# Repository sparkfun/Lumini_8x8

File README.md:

SparkFun LuMini 8x8 Matrix
========================================

[*SparkFun LuMini LED matrix (COM-15047)*](https://www.sparkfun.com/products/15047)

The LuMini 8x8 Matrix is a great way to add a square of light to just about anything, or even make a screen of a custom shape. The LuMini product line uses the same LED used on our Lumenati boards, the APA102, just in a smaller, 2.0x2.0 mm package. This allows for incredibly tight pixel densities, and thus, a screen with less pixelation. 

Repository Contents
-------------------

* **/Firmware** - Example code 
* **/Hardware** - Eagle design files (.brd, .sch)
* **/Production** - Production panel files (.brd)

Documentation
--------------
* **[Hookup Guide](https://learn.sparkfun.com/tutorials/lumini-8x8-matrix-hookup-guide)** - Basic hookup guide for the LuMini 8x8 LED Matrix.

Product Versions
----------------
* [COM-15047](https://www.sparkfun.com/products/15047)- 8x8 matrix of APA102 LED's packed into a single square inch.

License Information
-------------------

This product is _**open source**_! 

Please review the LICENSE.md file for license information. 

If you have any questions or concerns on licensing, please contact techsupport@sparkfun.com.

Distributed as-is; no warranty is given.

- Your friends at SparkFun.

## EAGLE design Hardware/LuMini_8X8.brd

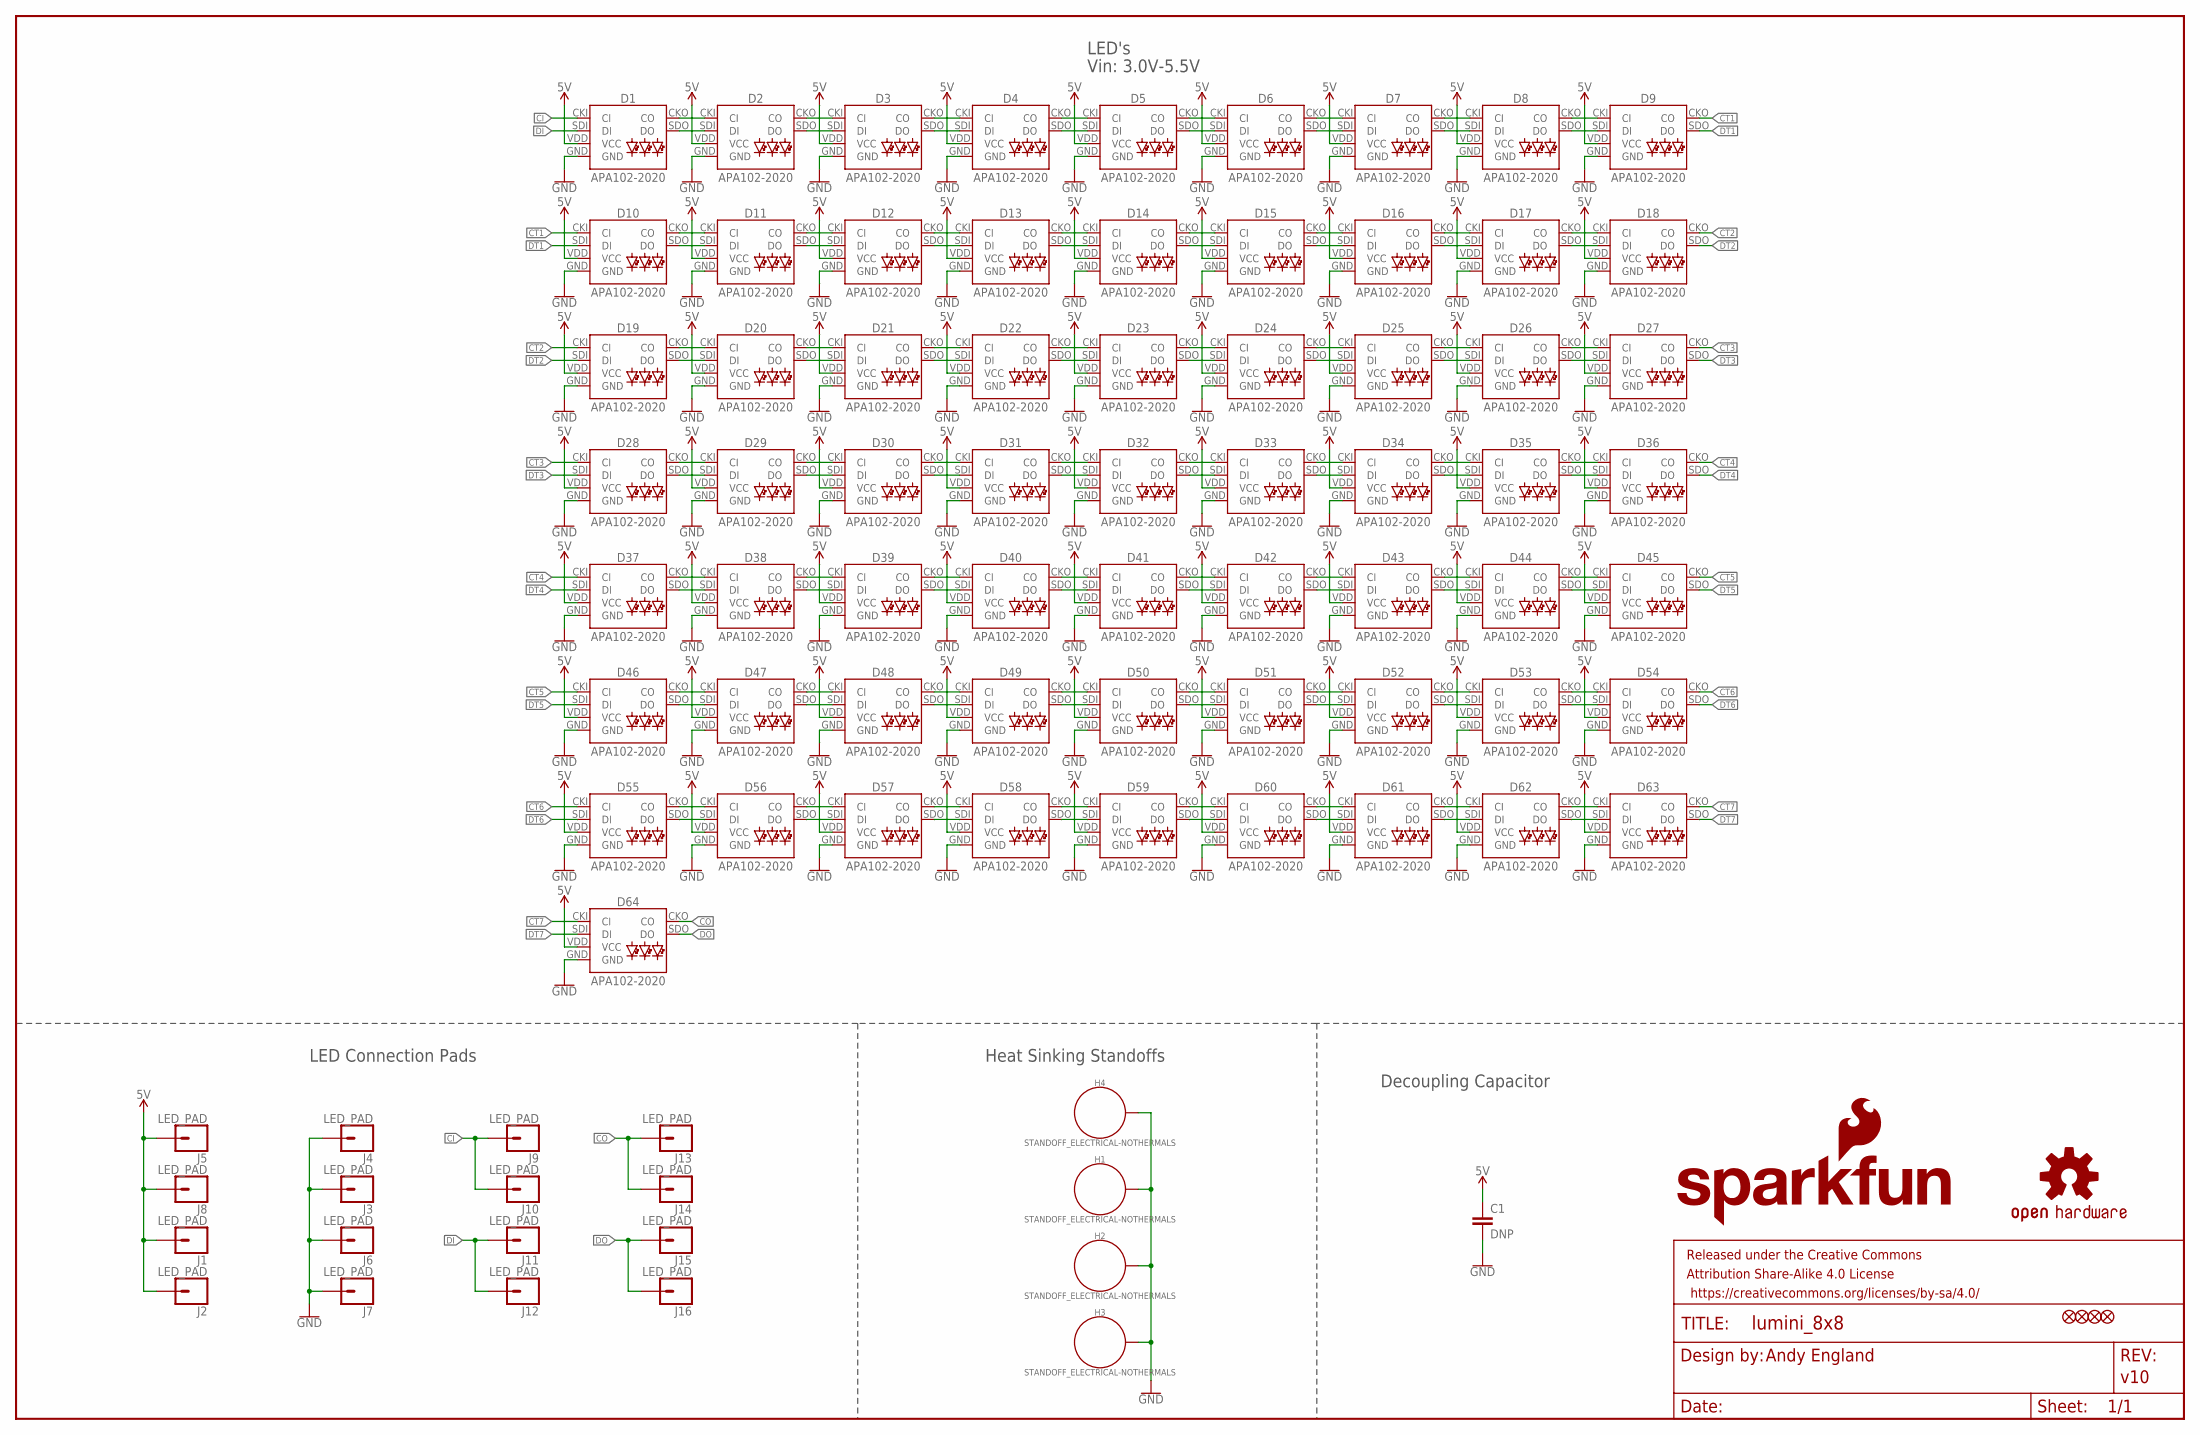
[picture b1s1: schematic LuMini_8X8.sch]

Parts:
C1: DNP; 1206
D1, D2, D3, D4, D5, D6, D7, D8, D9, D10, D11, D12, D13, D14, D15, D16, D17, D18, D19, D20, D21, D22, D23, D24, D25, D26, D27, D28, D29, D30, D31, D32, D33, D34, D35, D36, D37, D38, D39, D40, D41, D42, D43, D44, D45, D46, D47, D48, D49, D50, D51, D52, D53, D54, D55, D56, D57, D58, D59, D60, D61, D62, D63, D64: APA102-2020
FD1, FD2, FD3, FD4: FIDUCIALUFIDUCIAL; FIDUCIAL-MICRO
FRAME1: FRAME-LEDGER; CREATIVE_COMMONS
H1, H2, H3, H4: STANDOFF_ELECTRICAL-NOTHERMALS; STANDOFF-ELECTRICAL-NOTHERMALS
J1, J2, J3, J4, J5, J6, J7, J8, J9, J10, J11, J12, J13, J14, J15, J16: LED_PAD; CIRCULARPAD
LOGO1: SFE_LOGO_NAME_FLAME.1_INCH; SFE_LOGO_NAME_FLAME_.1
LOGO2: OSHW-LOGOS; OSHW-LOGO-S

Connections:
5V: C1.1, D1.VDD (VCC), D2.VDD (VCC), D3.VDD (VCC), D4.VDD (VCC), D5.VDD (VCC), D6.VDD (VCC), D7.VDD (VCC), D8.VDD (VCC), D9.VDD (VCC), D10.VDD (VCC), D11.VDD (VCC), D12.VDD (VCC), D13.VDD (VCC), D14.VDD (VCC), D15.VDD (VCC), D16.VDD (VCC), D17.VDD (VCC), D18.VDD (VCC), D19.VDD (VCC), D20.VDD (VCC), D21.VDD (VCC), D22.VDD (VCC), D23.VDD (VCC), D24.VDD (VCC), D25.VDD (VCC), D26.VDD (VCC), D27.VDD (VCC), D28.VDD (VCC), D29.VDD (VCC), D30.VDD (VCC), D31.VDD (VCC), D32.VDD (VCC), D33.VDD (VCC), D34.VDD (VCC), D35.VDD (VCC), D36.VDD (VCC), D37.VDD (VCC), D38.VDD (VCC), D39.VDD (VCC), D40.VDD (VCC), D41.VDD (VCC), D42.VDD (VCC), D43.VDD (VCC), D44.VDD (VCC), D45.VDD (VCC), D46.VDD (VCC), D47.VDD (VCC), D48.VDD (VCC), D49.VDD (VCC), D50.VDD (VCC), D51.VDD (VCC), D52.VDD (VCC), D53.VDD (VCC), D54.VDD (VCC), D55.VDD (VCC), D56.VDD (VCC), D57.VDD (VCC), D58.VDD (VCC), D59.VDD (VCC), D60.VDD (VCC), D61.VDD (VCC), D62.VDD (VCC), D63.VDD (VCC), D64.VDD (VCC), J1.P$1, J1.P$2, J2.P$1, J2.P$2, J5.P$1, J5.P$2, J8.P$1, J8.P$2
CI: D1.CKI (CI), J9.P$1, J9.P$2, J10.P$1, J10.P$2
CO: D64.CKO (CO), J13.P$1, J13.P$2, J14.P$1, J14.P$2
CT1: D9.CKO (CO), D10.CKI (CI)
CT2: D18.CKO (CO), D19.CKI (CI)
CT3: D27.CKO (CO), D28.CKI (CI)
CT4: D36.CKO (CO), D37.CKI (CI)
CT5: D45.CKO (CO), D46.CKI (CI)
CT6: D54.CKO (CO), D55.CKI (CI)
CT7: D63.CKO (CO), D64.CKI (CI)
DI: D1.SDI (DI), J11.P$1, J11.P$2, J12.P$1, J12.P$2
DO: D64.SDO (DO), J15.P$1, J15.P$2, J16.P$1, J16.P$2
DT1: D9.SDO (DO), D10.SDI (DI)
DT2: D18.SDO (DO), D19.SDI (DI)
DT3: D27.SDO (DO), D28.SDI (DI)
DT4: D36.SDO (DO), D37.SDI (DI)
DT5: D45.SDO (DO), D46.SDI (DI)
DT6: D54.SDO (DO), D55.SDI (DI)
DT7: D63.SDO (DO), D64.SDI (DI)
GND: C1.2, D1.GND, D2.GND, D3.GND, D4.GND, D5.GND, D6.GND, D7.GND, D8.GND, D9.GND, D10.GND, D11.GND, D12.GND, D13.GND, D14.GND, D15.GND, D16.GND, D17.GND, D18.GND, D19.GND, D20.GND, D21.GND, D22.GND, D23.GND, D24.GND, D25.GND, D26.GND, D27.GND, D28.GND, D29.GND, D30.GND, D31.GND, D32.GND, D33.GND, D34.GND, D35.GND, D36.GND, D37.GND, D38.GND, D39.GND, D40.GND, D41.GND, D42.GND, D43.GND, D44.GND, D45.GND, D46.GND, D47.GND, D48.GND, D49.GND, D50.GND, D51.GND, D52.GND, D53.GND, D54.GND, D55.GND, D56.GND, D57.GND, D58.GND, D59.GND, D60.GND, D61.GND, D62.GND, D63.GND, D64.GND, H1.P1, H2.P1, H3.P1, H4.P1, J3.P$1, J3.P$2, J4.P$1, J4.P$2, J6.P$1, J6.P$2, J7.P$1, J7.P$2
unnamed: D1.SDO (DO), D2.SDI (DI)
unnamed: D1.CKO (CO), D2.CKI (CI)
unnamed: D2.SDO (DO), D3.SDI (DI)
unnamed: D2.CKO (CO), D3.CKI (CI)
unnamed: D3.SDO (DO), D4.SDI (DI)
unnamed: D3.CKO (CO), D4.CKI (CI)
unnamed: D4.SDO (DO), D5.SDI (DI)
unnamed: D4.CKO (CO), D5.CKI (CI)
unnamed: D5.SDO (DO), D6.SDI (DI)
unnamed: D5.CKO (CO), D6.CKI (CI)
unnamed: D6.SDO (DO), D7.SDI (DI)
unnamed: D6.CKO (CO), D7.CKI (CI)
unnamed: D7.SDO (DO), D8.SDI (DI)
unnamed: D7.CKO (CO), D8.CKI (CI)
unnamed: D8.SDO (DO), D9.SDI (DI)
unnamed: D8.CKO (CO), D9.CKI (CI)
unnamed: D10.SDO (DO), D11.SDI (DI)
unnamed: D10.CKO (CO), D11.CKI (CI)
unnamed: D11.SDO (DO), D12.SDI (DI)
unnamed: D11.CKO (CO), D12.CKI (CI)
unnamed: D12.SDO (DO), D13.SDI (DI)
unnamed: D12.CKO (CO), D13.CKI (CI)
unnamed: D13.SDO (DO), D14.SDI (DI)
unnamed: D13.CKO (CO), D14.CKI (CI)
unnamed: D14.SDO (DO), D15.SDI (DI)
unnamed: D14.CKO (CO), D15.CKI (CI)
unnamed: D15.SDO (DO), D16.SDI (DI)
unnamed: D15.CKO (CO), D16.CKI (CI)
unnamed: D16.SDO (DO), D17.SDI (DI)
unnamed: D16.CKO (CO), D17.CKI (CI)
unnamed: D17.SDO (DO), D18.SDI (DI)
unnamed: D17.CKO (CO), D18.CKI (CI)
unnamed: D19.SDO (DO), D20.SDI (DI)
unnamed: D19.CKO (CO), D20.CKI (CI)
unnamed: D20.SDO (DO), D21.SDI (DI)
unnamed: D20.CKO (CO), D21.CKI (CI)
unnamed: D21.SDO (DO), D22.SDI (DI)
unnamed: D21.CKO (CO), D22.CKI (CI)
unnamed: D22.SDO (DO), D23.SDI (DI)
unnamed: D22.CKO (CO), D23.CKI (CI)
unnamed: D23.SDO (DO), D24.SDI (DI)
unnamed: D23.CKO (CO), D24.CKI (CI)
unnamed: D24.SDO (DO), D25.SDI (DI)
unnamed: D24.CKO (CO), D25.CKI (CI)
unnamed: D25.SDO (DO), D26.SDI (DI)
unnamed: D25.CKO (CO), D26.CKI (CI)
unnamed: D26.SDO (DO), D27.SDI (DI)
unnamed: D26.CKO (CO), D27.CKI (CI)
unnamed: D28.SDO (DO), D29.SDI (DI)
unnamed: D28.CKO (CO), D29.CKI (CI)
unnamed: D29.SDO (DO), D30.SDI (DI)
unnamed: D29.CKO (CO), D30.CKI (CI)
unnamed: D30.SDO (DO), D31.SDI (DI)
unnamed: D30.CKO (CO), D31.CKI (CI)
unnamed: D31.SDO (DO), D32.SDI (DI)
unnamed: D31.CKO (CO), D32.CKI (CI)
unnamed: D32.SDO (DO), D33.SDI (DI)
unnamed: D32.CKO (CO), D33.CKI (CI)
unnamed: D33.SDO (DO), D34.SDI (DI)
unnamed: D33.CKO (CO), D34.CKI (CI)
unnamed: D34.SDO (DO), D35.SDI (DI)
unnamed: D34.CKO (CO), D35.CKI (CI)
unnamed: D35.SDO (DO), D36.SDI (DI)
unnamed: D35.CKO (CO), D36.CKI (CI)
unnamed: D37.SDO (DO), D38.SDI (DI)
unnamed: D37.CKO (CO), D38.CKI (CI)
unnamed: D38.SDO (DO), D39.SDI (DI)
unnamed: D38.CKO (CO), D39.CKI (CI)
unnamed: D39.SDO (DO), D40.SDI (DI)
unnamed: D39.CKO (CO), D40.CKI (CI)
unnamed: D40.SDO (DO), D41.SDI (DI)
unnamed: D40.CKO (CO), D41.CKI (CI)
unnamed: D41.SDO (DO), D42.SDI (DI)
unnamed: D41.CKO (CO), D42.CKI (CI)
unnamed: D42.SDO (DO), D43.SDI (DI)
unnamed: D42.CKO (CO), D43.CKI (CI)
unnamed: D43.SDO (DO), D44.SDI (DI)
unnamed: D43.CKO (CO), D44.CKI (CI)
unnamed: D44.SDO (DO), D45.SDI (DI)
unnamed: D44.CKO (CO), D45.CKI (CI)
unnamed: D46.SDO (DO), D47.SDI (DI)
unnamed: D46.CKO (CO), D47.CKI (CI)
unnamed: D47.SDO (DO), D48.SDI (DI)
unnamed: D47.CKO (CO), D48.CKI (CI)
unnamed: D48.SDO (DO), D49.SDI (DI)
unnamed: D48.CKO (CO), D49.CKI (CI)
unnamed: D49.SDO (DO), D50.SDI (DI)
unnamed: D49.CKO (CO), D50.CKI (CI)
unnamed: D50.SDO (DO), D51.SDI (DI)
unnamed: D50.CKO (CO), D51.CKI (CI)
unnamed: D51.SDO (DO), D52.SDI (DI)
unnamed: D51.CKO (CO), D52.CKI (CI)
unnamed: D52.SDO (DO), D53.SDI (DI)
unnamed: D52.CKO (CO), D53.CKI (CI)
unnamed: D53.SDO (DO), D54.SDI (DI)
unnamed: D53.CKO (CO), D54.CKI (CI)
unnamed: D55.SDO (DO), D56.SDI (DI)
unnamed: D55.CKO (CO), D56.CKI (CI)
unnamed: D56.SDO (DO), D57.SDI (DI)
unnamed: D56.CKO (CO), D57.CKI (CI)
unnamed: D57.SDO (DO), D58.SDI (DI)
unnamed: D57.CKO (CO), D58.CKI (CI)
unnamed: D58.SDO (DO), D59.SDI (DI)
unnamed: D58.CKO (CO), D59.CKI (CI)
unnamed: D59.SDO (DO), D60.SDI (DI)
unnamed: D59.CKO (CO), D60.CKI (CI)
unnamed: D60.SDO (DO), D61.SDI (DI)
unnamed: D60.CKO (CO), D61.CKI (CI)
unnamed: D61.SDO (DO), D62.SDI (DI)
unnamed: D61.CKO (CO), D62.CKI (CI)
unnamed: D62.SDO (DO), D63.SDI (DI)
unnamed: D62.CKO (CO), D63.CKI (CI)

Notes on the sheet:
LED's
Heat Sinking Standoffs
Andy England
v10
LED Connection Pads
Decoupling Capacitor
Vin: 3.0V-5.5V

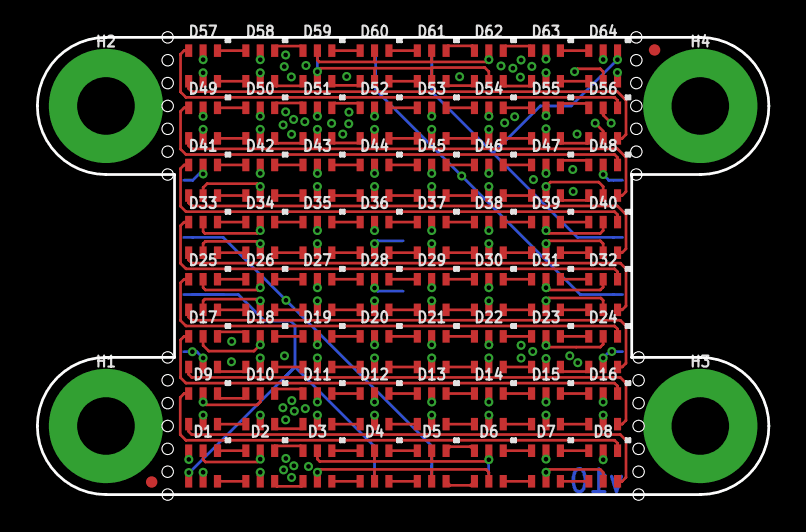
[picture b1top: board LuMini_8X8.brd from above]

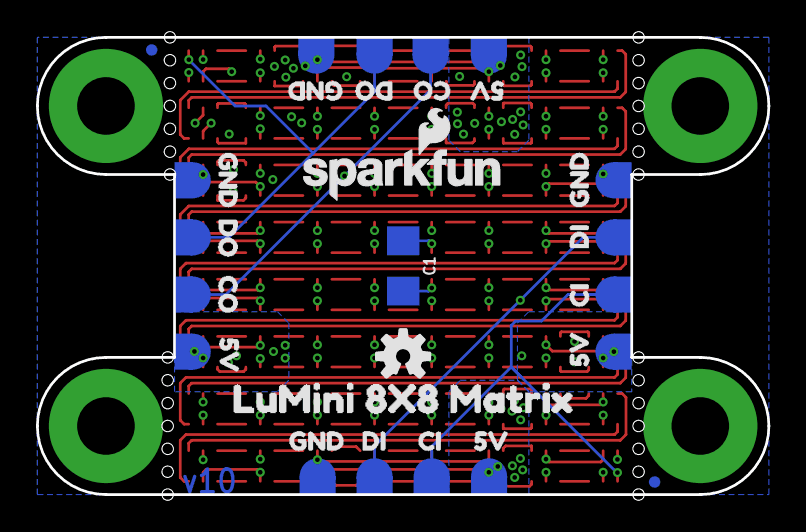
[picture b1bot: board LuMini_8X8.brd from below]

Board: 4 copper layers, 40.6 x 25.4 mm, 110 parts (38 on the bottom side), 132 nets.

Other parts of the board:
U$1, U$2, U$11, U$18: 5V5
U$3, U$12: CI1
U$4, U$17: CO3
U$5, U$13: DI2
U$6, U$16: DO4
U$7, U$8, U$14, U$15: GND6
U$9: LUMINI_8X8_MATRIX0
U$10: ORDERING_INSTRUCTIONS

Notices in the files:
parts and their libraries:
SparkFun-LED: Licensing: Creative Commons ShareAlike 4.0 International - https://creativecommons.org/licenses/by-sa/4.0
SparkFun-Aesthetics: Released under the Creative Commons Attribution Share-Alike 4.0 License
SparkFun-Aesthetics: https://creativecommons.org/licenses/by-sa/4.0
